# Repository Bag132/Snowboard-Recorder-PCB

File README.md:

# Snowboard-Recorder-PCB
## Purpose
I designed this board for a Software Engineering class project. The PCB was made to facilitate communication between a ESP32-WROVER SoC and BNO086 IMU which the ESP32 then reports constant updates to a mobile app through Bluetooth. In practice, the PCB is installed into a housing which is then mounted on a snowboard.
## Remarks
I2C should not have been used to communicate with the BNO086 because the updated ESP32 I2C driver does not support SCL-stretching, which the BNO086 needs to communicate without issues arising. Only the legacy ESP-IDF driver consisitently works with it. SPI should have been used in place of I2C.
## Pictures

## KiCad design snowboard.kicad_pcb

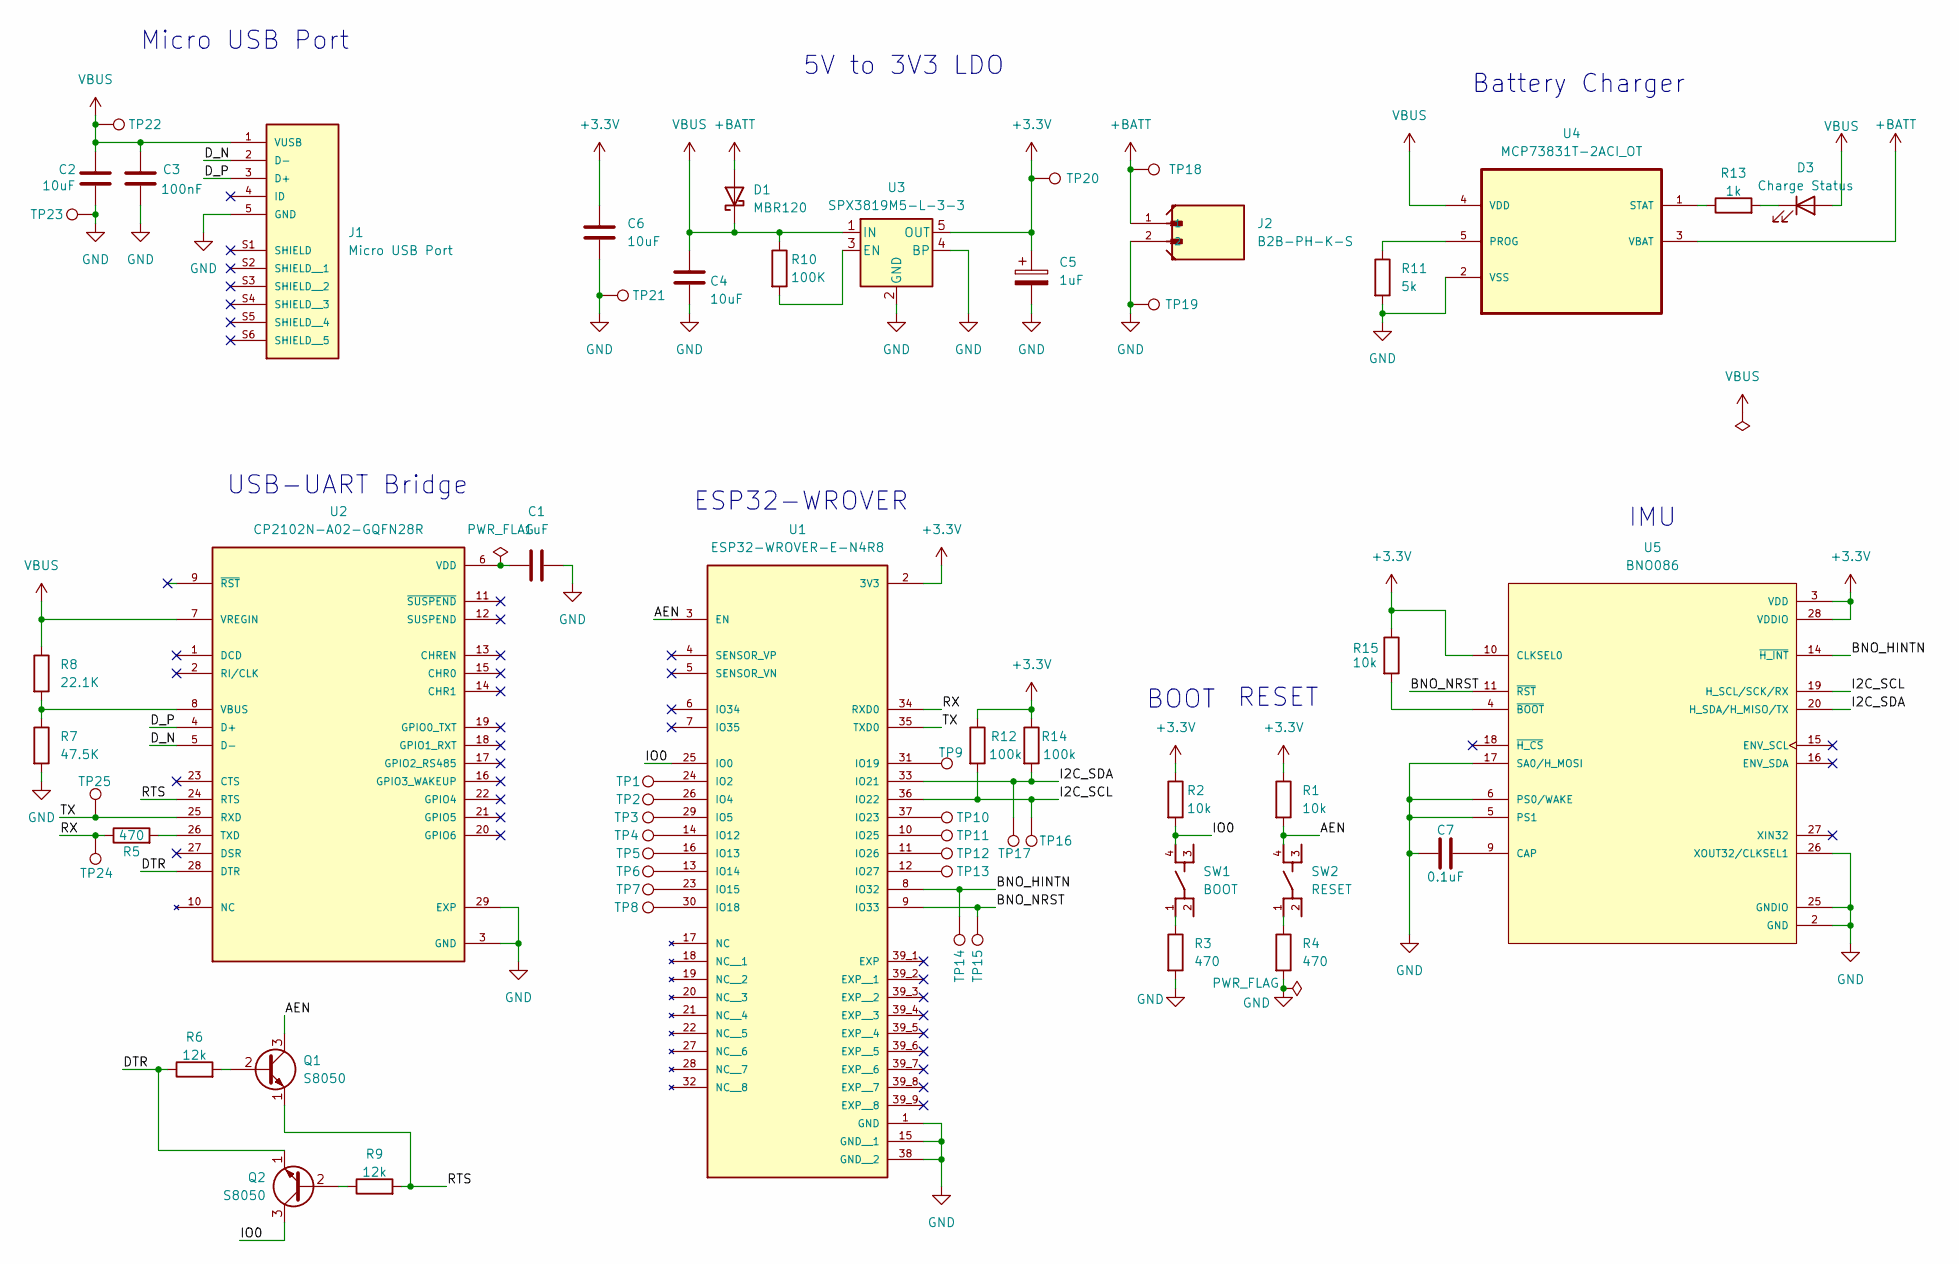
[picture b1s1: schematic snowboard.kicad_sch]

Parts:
C1, C5: 1uF
C2, C4, C6: 10uF
C3: 100nF
C7: 0.1uF
D1: MBR120
D3: Charge Status
J1: Micro USB Port; AMPHENOL_10118193-0001LF; PARTREV E
J2: B2B-PH-K-S; JST_B2B-PH-K-S
Q1, Q2: S8050; TO-92_Inline
R1, R2, R15: 10k
R3, R4, R5: 470
R6, R9: 12k
R7: 47.5K
R8: 22.1K
R10: 100K
R11: 5k
R12, R14: 100k
R13: 1k
SW1: BOOT; SW_PTS810_SJM_250_SMTR_LFS
SW2: RESET; SW_PTS810_SJM_250_SMTR_LFS
TP1, TP2, TP3, TP4, TP5, TP6, TP7, TP8, TP9, TP10, TP11, TP12, TP13, TP14, TP15, TP16, TP17, TP18, TP19, TP20, TP21, TP22, TP23, TP24, TP25: TestPoint
U1: ESP32-WROVER-E-N4R8; XCVR_ESP32-WROVER-E-N4R8; PARTREV 1.6
U2: CP2102N-A02-GQFN28R; IC_CP2102N-A02-GQFN28R; PARTREV 1.5
U3: SPX3819M5-L-3-3; SOT-23-5
U4: MCP73831T-2ACI_OT; SOT95P280X145-5N; MPN MCP73831T-2ACI/OT
U5: BNO086; IC_BNO080; PARTREV 1.6

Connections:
+3.3V: C5.1, C6.1, R1.1, R2.1, R12.1, R14.1, R15.1, TP20.1, U1.2 (3V3), U3.5 (OUT), U5.3 (VDD), U5.10 (CLKSEL0), U5.28 (VDDIO)
+BATT: D1.2 (A), J2.1, TP18.1, U4.3 (VBAT)
/AEN: Q1.3 (C), R1.2, SW2.4, U1.3 (EN)
/BNO_HINTN: TP14.1, U1.8 (IO32), U5.14 (~H_INT)
/BNO_NRST: TP15.1, U1.9 (IO33), U5.11 (~RST)
/DTR: Q2.1 (E), R6.1, U2.28 (DTR)
/D_N: J1.2 (D-), U2.5 (D-)
/D_P: J1.3 (D+), U2.4 (D+)
/I2C_SCL: R12.2, TP16.1, U1.36 (IO22), U5.19 (H_SCL/SCK/RX)
/I2C_SDA: R14.2, TP17.1, U1.33 (IO21), U5.20 (H_SDA/H_MISO/TX)
/IO0: Q2.3 (C), R2.2, SW1.4, U1.25 (IO0)
/RTS: Q1.1 (E), R9.2, U2.24 (RTS)
/RX: R5.1, TP24.1, U1.34 (RXD0)
/TX: TP25.1, U1.35 (TXD0), U2.25 (RXD)
GND: C1.2, C2.2, C3.2, C4.2, C5.2, C6.2, C7.1, J1.5 (GND), J2.2, R3.2, R4.2, R7.2, R11.2, TP19.1, TP21.1, TP23.1, U1.1 (GND), U1.15 (GND__1), U1.38 (GND__2), U2.3 (GND), U2.29 (EXP), U3.2 (GND), U3.4 (BP), U4.2 (VSS), U5.2 (GND), U5.5 (PS1), U5.6 (PS0/WAKE), U5.17 (SA0/H_MOSI), U5.25 (GNDIO), U5.26 (XOUT32/CLKSEL1)
unnamed: D3.1 (K), R13.2
unnamed: Q1.2 (B), R6.2
unnamed: Q2.2 (B), R9.1
unnamed: R3.1, SW1.1
unnamed: R4.1, SW2.1
unnamed: TP1.1, U1.24 (IO2)
unnamed: TP2.1, U1.26 (IO4)
unnamed: TP3.1, U1.29 (IO5)
unnamed: TP4.1, U1.14 (IO12)
unnamed: TP5.1, U1.16 (IO13)
unnamed: TP6.1, U1.13 (IO14)
unnamed: TP7.1, U1.23 (IO15)
unnamed: TP8.1, U1.30 (IO18)
unnamed: TP9.1, U1.31 (IO19)
unnamed: TP10.1, U1.37 (IO23)
unnamed: TP11.1, U1.10 (IO25)
unnamed: TP12.1, U1.11 (IO26)
unnamed: TP13.1, U1.12 (IO27)
unnamed: R5.2, U2.26 (TXD)
unnamed: R7.1, R8.2, U2.8 (VBUS)
unnamed: C1.1, U2.6 (VDD)
unnamed: R10.2, U3.3 (EN)
unnamed: R11.1, U4.5 (PROG)
unnamed: R13.1, U4.1 (STAT)
unnamed: C7.2, U5.9 (CAP)
unnamed: R15.2, U5.4 (~BOOT)
VBUS: C2.1, C3.1, C4.1, D1.1 (K), D3.2 (A), J1.1 (VUSB), R8.1, R10.1, TP22.1, U2.7 (VREGIN), U3.1 (IN), U4.4 (VDD)

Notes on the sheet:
USB-UART Bridge
IMU
Battery Charger
Micro USB Port
ESP32-WROVER
RESET
5V to 3V3 LDO
BOOT

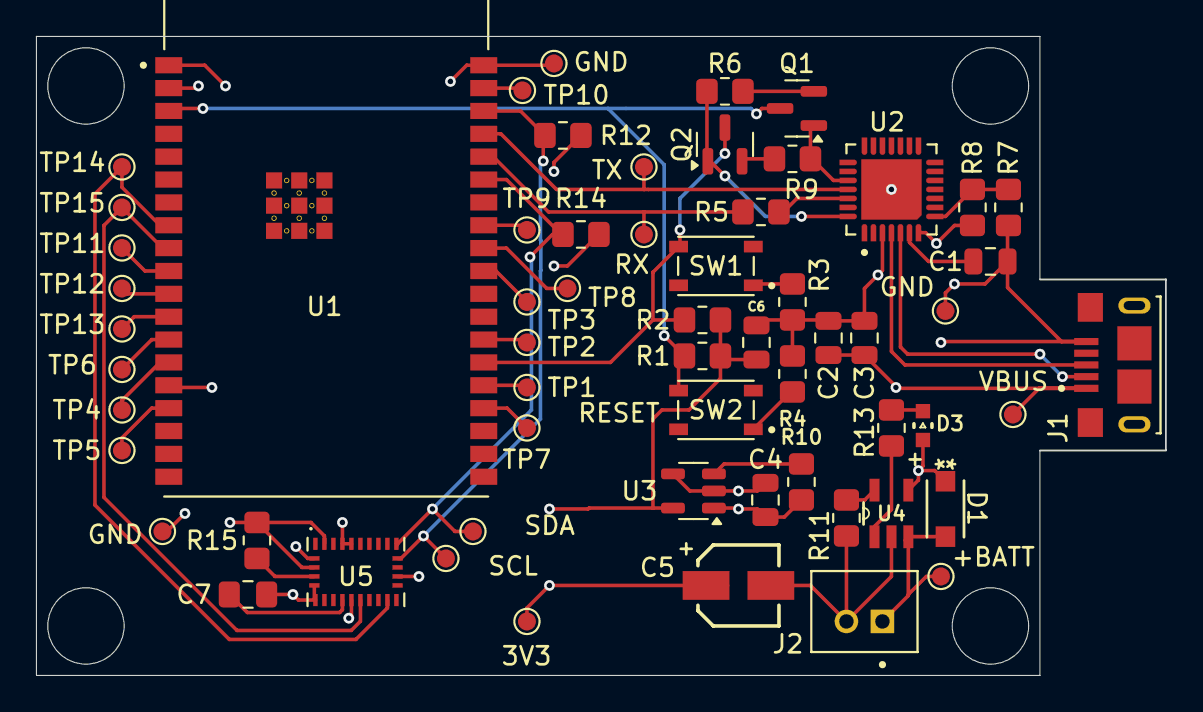
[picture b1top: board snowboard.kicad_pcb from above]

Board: 4 copper layers, 62.7 x 35.5 mm, 60 parts (0 on the bottom side), 42 nets.

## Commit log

2025-02-04 Base ESP Schematic
2025-02-06 Started PCB
2025-02-06 Update battery connector
2025-02-06 Add footprints and models and place components on PCB
2025-02-06 PCB routing mostly done
2025-02-06 Add IMU
2025-02-06 Add test points
2025-02-07 Swap discontinued MPU6050 for BNO086
2025-02-07 Fix track spacing
2025-04-12 Reduce i2c pull-up value, fix shorting LDO, DNP auto-reset
